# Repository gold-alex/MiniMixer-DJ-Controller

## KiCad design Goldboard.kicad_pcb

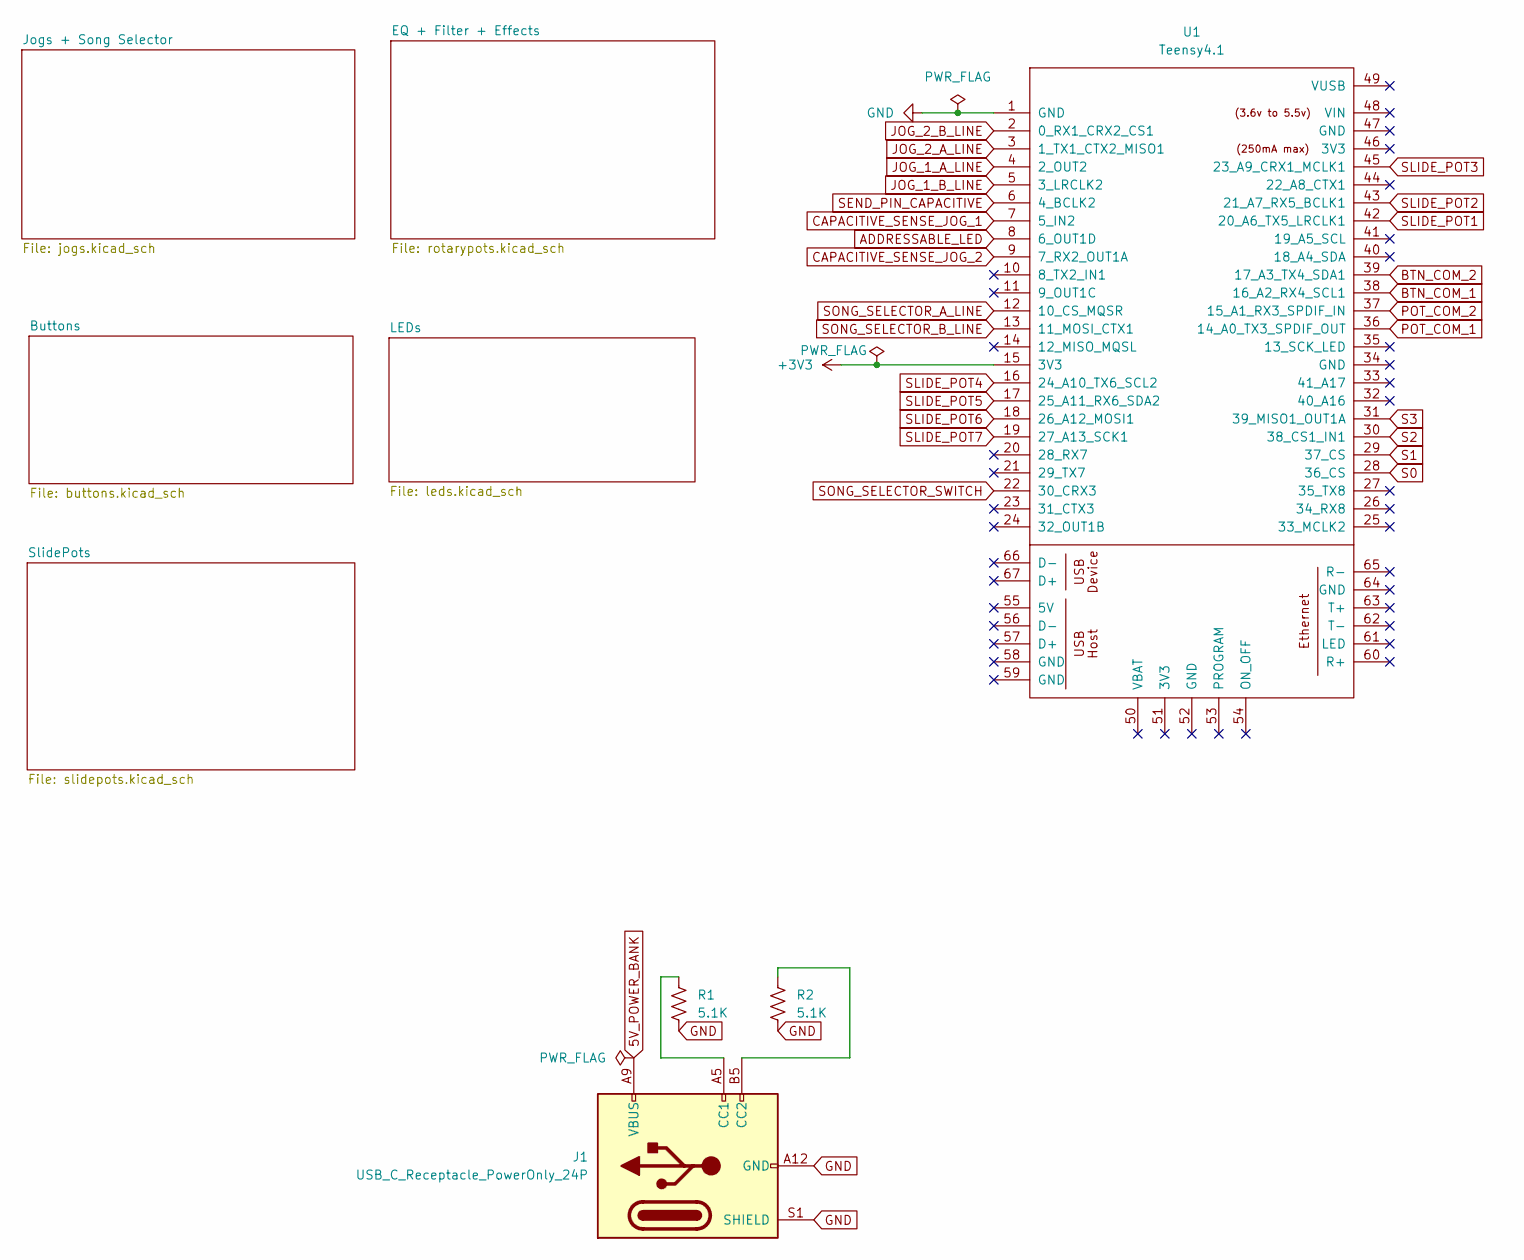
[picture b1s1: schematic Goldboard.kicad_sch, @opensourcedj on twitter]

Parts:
J1: USB_C_Receptacle_PowerOnly_24P; AMPHENOL_12401832E402A
R1, R2: 5.1K; R_0603_1608Metric
U1: Teensy4.1; Teensy41

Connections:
5V_POWER_BANK: J1.A4 (VBUS), J1.A9 (VBUS), J1.B4 (VBUS), J1.B9 (VBUS); also elsewhere on the board
+3V3: U1.15 (3V3); also elsewhere on the board
ADDRESSABLE_LED: U1.8 (6_OUT1D); also elsewhere on the board
BTN_COM_1: U1.38 (16_A2_RX4_SCL1); also elsewhere on the board
BTN_COM_2: U1.39 (17_A3_TX4_SDA1); also elsewhere on the board
CAPACITIVE_SENSE_JOG_1: U1.7 (5_IN2); also elsewhere on the board
CAPACITIVE_SENSE_JOG_2: U1.9 (7_RX2_OUT1A); also elsewhere on the board
GND: J1.A1 (GND), J1.A12 (GND), J1.B1 (GND), J1.B12 (GND), J1.S1 (SHIELD), R1.2, R2.2, U1.1 (GND); also elsewhere on the board
JOG_1_A_LINE: U1.4 (2_OUT2); also elsewhere on the board
JOG_1_B_LINE: U1.5 (3_LRCLK2); also elsewhere on the board
JOG_2_A_LINE: U1.3 (1_TX1_CTX2_MISO1); also elsewhere on the board
JOG_2_B_LINE: U1.2 (0_RX1_CRX2_CS1); also elsewhere on the board
unnamed: J1.A5 (CC1), R1.1
unnamed: J1.B5 (CC2), R2.1
POT_COM_1: U1.36 (14_A0_TX3_SPDIF_OUT); also elsewhere on the board
POT_COM_2: U1.37 (15_A1_RX3_SPDIF_IN); also elsewhere on the board
S0: U1.28 (36_CS); also elsewhere on the board
S1: U1.29 (37_CS); also elsewhere on the board
S2: U1.30 (38_CS1_IN1); also elsewhere on the board
S3: U1.31 (39_MISO1_OUT1A); also elsewhere on the board
SEND_PIN_CAPACITIVE: U1.6 (4_BCLK2); also elsewhere on the board
SLIDE_POT1: U1.42 (20_A6_TX5_LRCLK1); also elsewhere on the board
SLIDE_POT2: U1.43 (21_A7_RX5_BCLK1); also elsewhere on the board
SLIDE_POT3: U1.45 (23_A9_CRX1_MCLK1); also elsewhere on the board
SLIDE_POT4: U1.16 (24_A10_TX6_SCL2); also elsewhere on the board
SLIDE_POT5: U1.17 (25_A11_RX6_SDA2); also elsewhere on the board
SLIDE_POT6: U1.18 (26_A12_MOSI1); also elsewhere on the board
SLIDE_POT7: U1.19 (27_A13_SCK1); also elsewhere on the board
SONG_SELECTOR_A_LINE: U1.12 (10_CS_MQSR); also elsewhere on the board
SONG_SELECTOR_B_LINE: U1.13 (11_MOSI_CTX1); also elsewhere on the board
SONG_SELECTOR_SWITCH: U1.22 (30_CRX3); also elsewhere on the board

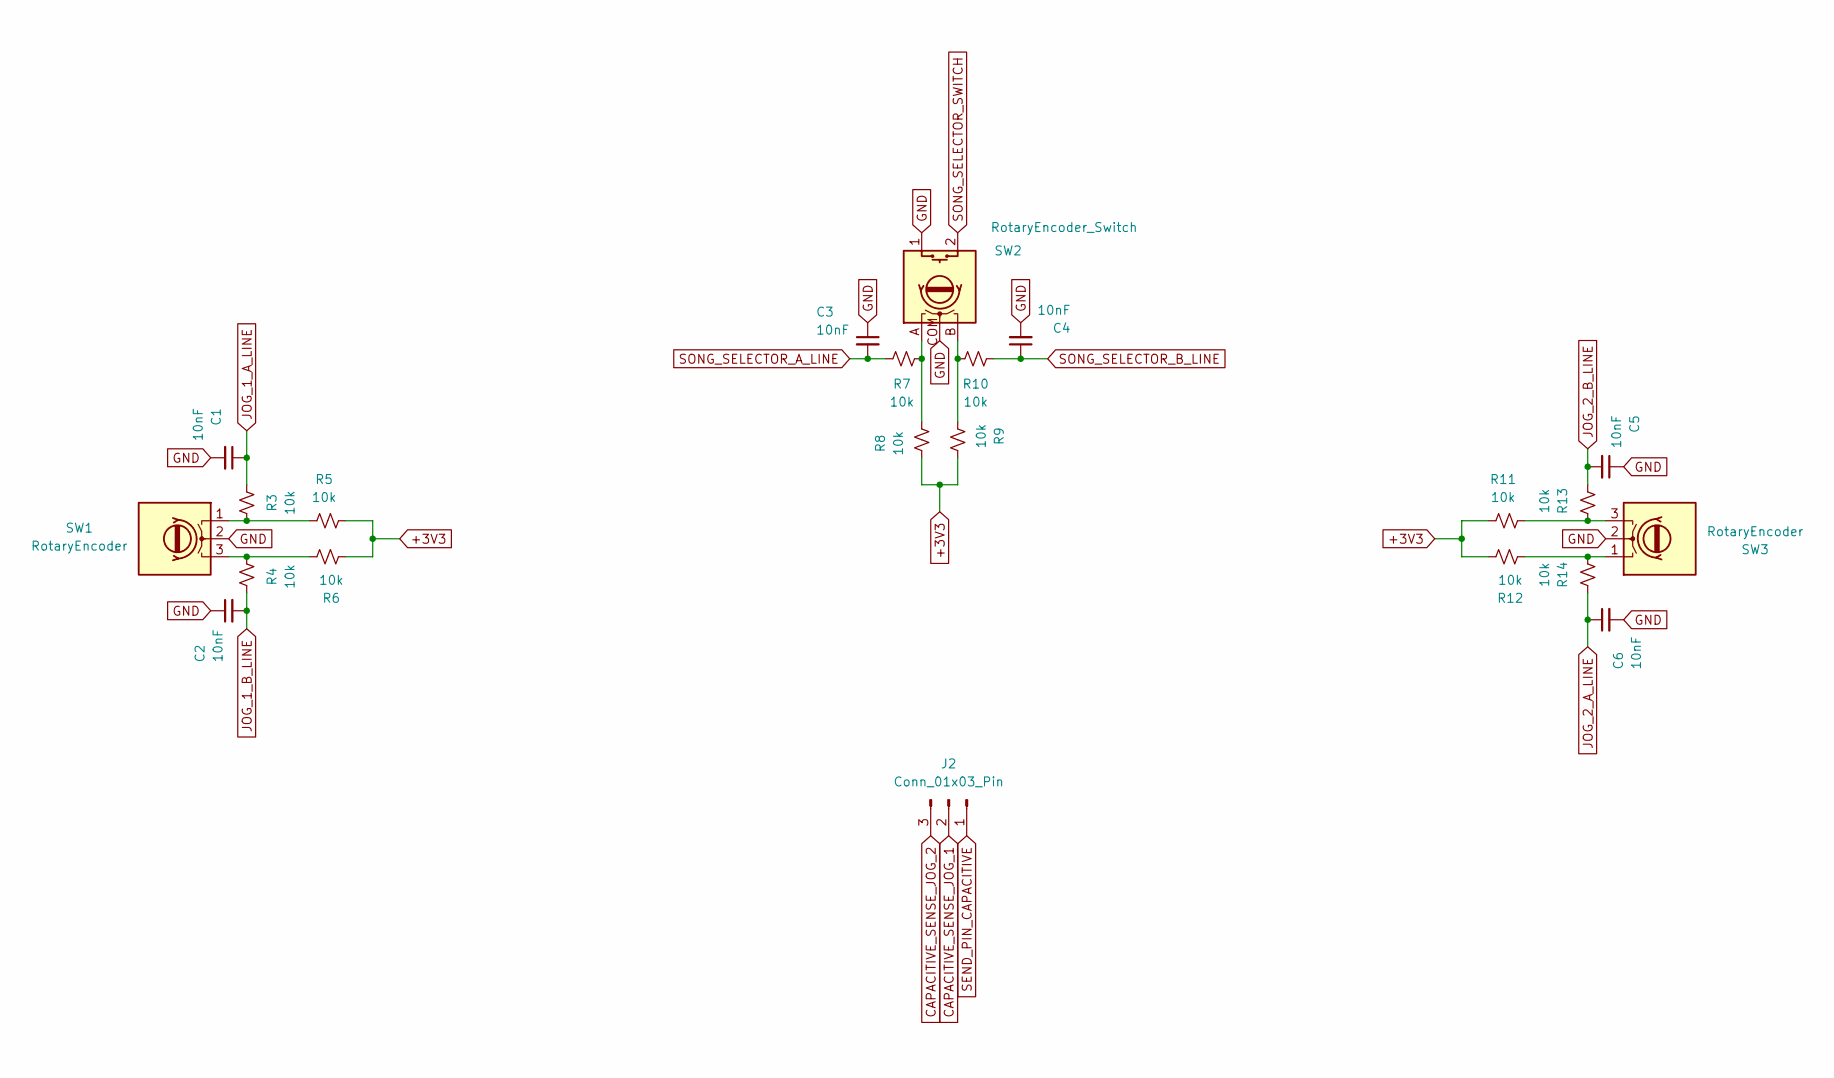
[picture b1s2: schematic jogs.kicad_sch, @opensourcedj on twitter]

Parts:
C1, C2, C3, C4, C5, C6: 10nF; C_0603_1608Metric
J2: Conn_01x03_Pin; PinHeader_1x03_P2.54mm_Horizontal
R3, R4, R5, R6, R7, R8, R9, R10, R11, R12, R13, R14: 10k; R_0603_1608Metric
SW1, SW3: RotaryEncoder; PEC11R-4x15F-Nxxxx_BRN
SW2: RotaryEncoder_Switch; XDCR_PEC11R-4215F-S0024

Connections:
+3V3: R5.1, R6.2, R8.2, R9.1, R11.2, R12.1; also elsewhere on the board
CAPACITIVE_SENSE_JOG_1: J2.2; also elsewhere on the board
CAPACITIVE_SENSE_JOG_2: J2.3; also elsewhere on the board
GND: C1.2, C2.1, C3.1, C4.2, C5.1, C6.2, SW1.2 (C), SW2.1 (S1), SW2.COM (C), SW3.2 (C); also elsewhere on the board
JOG_1_A_LINE: C1.1, R3.1; also elsewhere on the board
JOG_1_B_LINE: C2.2, R4.2; also elsewhere on the board
JOG_2_A_LINE: C6.1, R14.1; also elsewhere on the board
JOG_2_B_LINE: C5.2, R13.2; also elsewhere on the board
unnamed: R7.1, R8.1, SW2.A
unnamed: R9.2, R10.2, SW2.B
unnamed: R3.2, R5.2, SW1.1 (A)
unnamed: R4.1, R6.1, SW1.3 (B)
unnamed: R12.2, R14.2, SW3.1 (A)
unnamed: R11.1, R13.1, SW3.3 (B)
SEND_PIN_CAPACITIVE: J2.1; also elsewhere on the board
SONG_SELECTOR_A_LINE: C3.2, R7.2; also elsewhere on the board
SONG_SELECTOR_B_LINE: C4.1, R10.1; also elsewhere on the board
SONG_SELECTOR_SWITCH: SW2.2 (S2); also elsewhere on the board

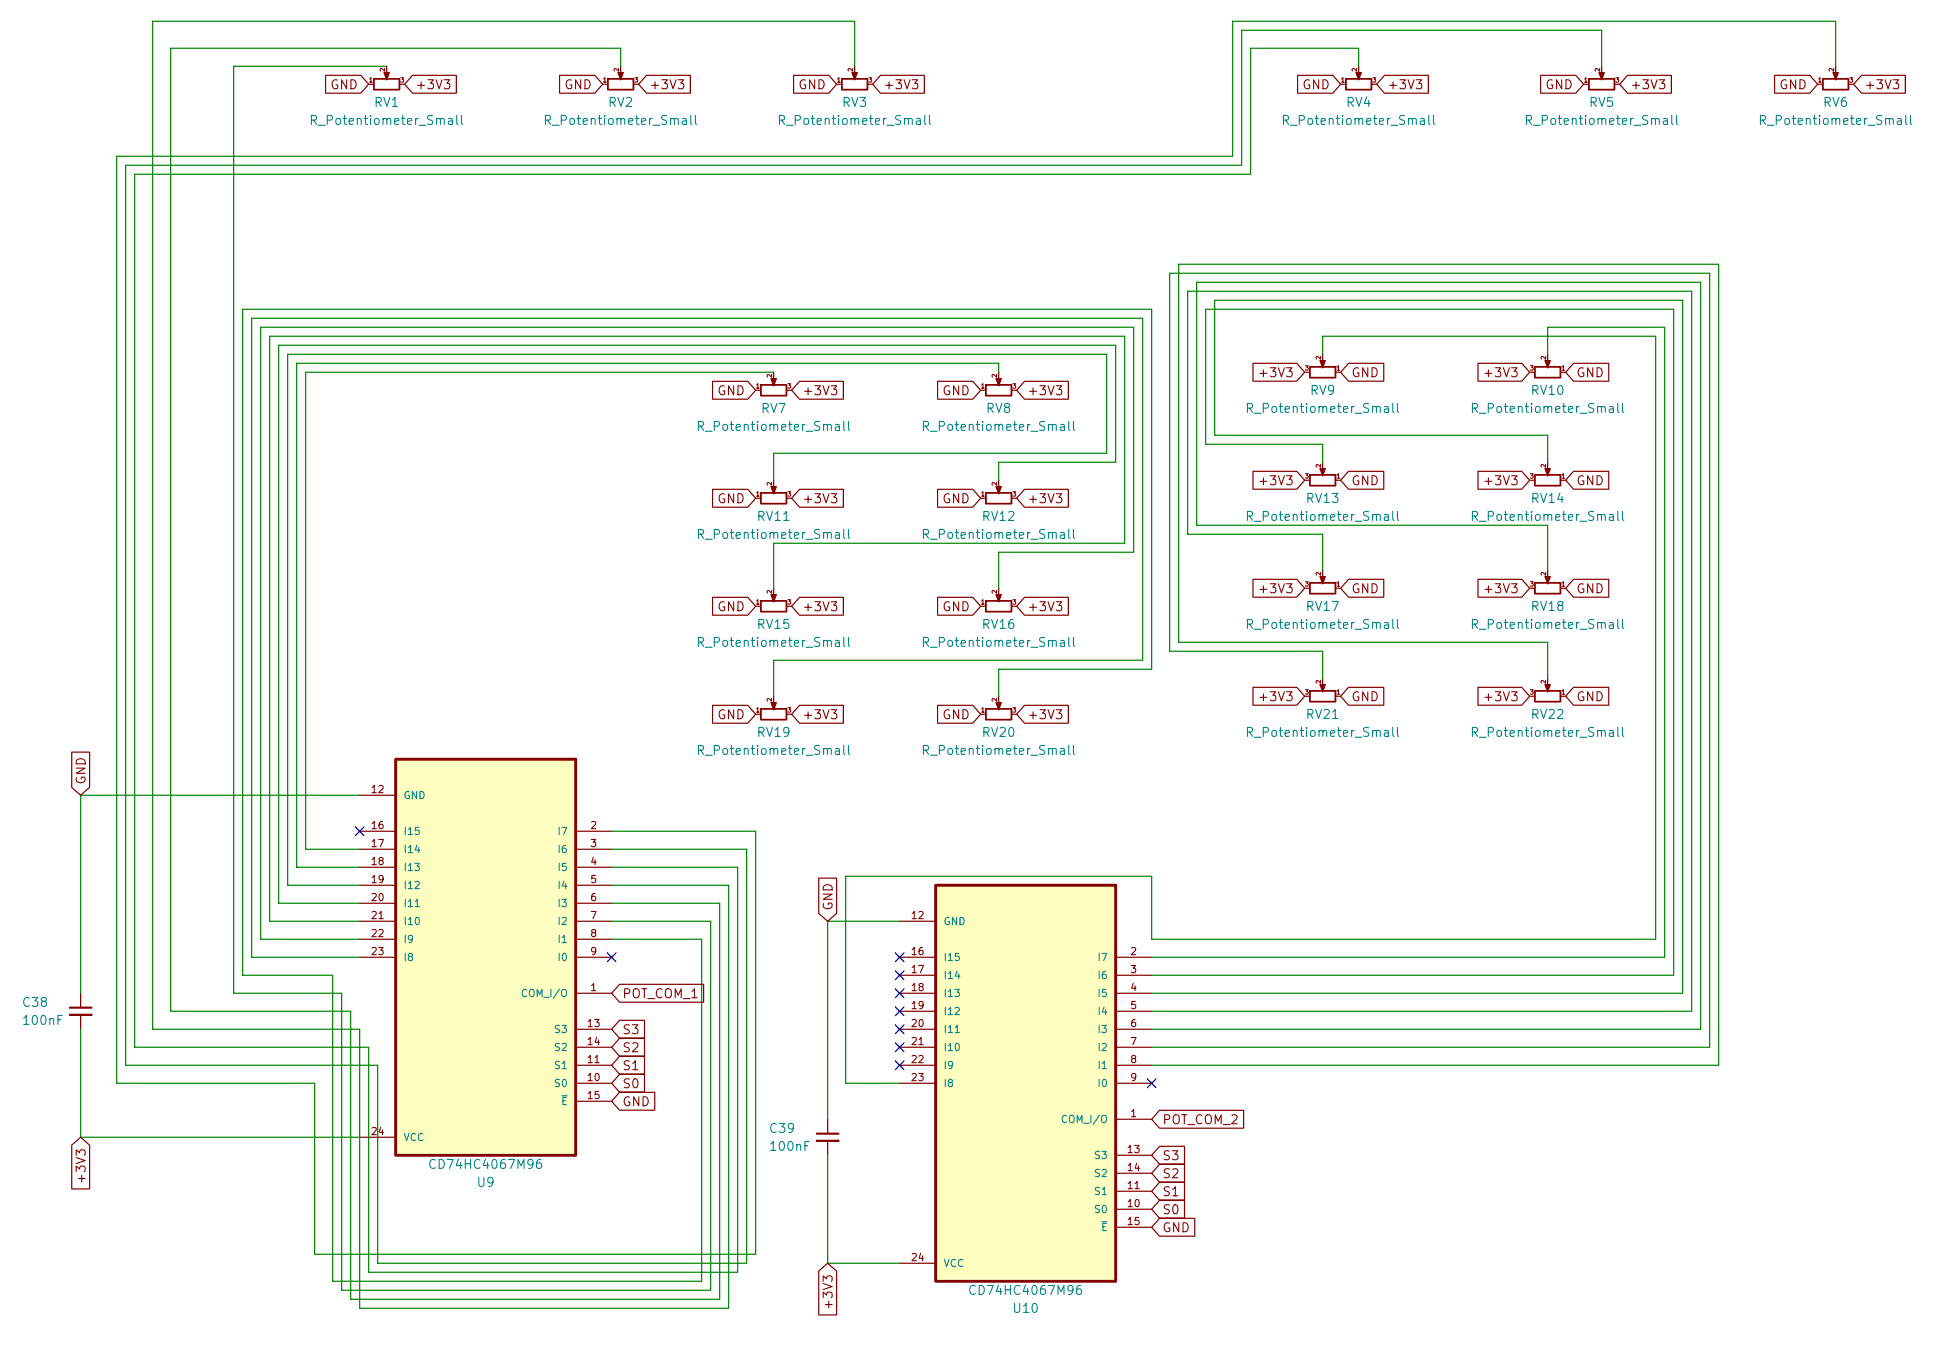
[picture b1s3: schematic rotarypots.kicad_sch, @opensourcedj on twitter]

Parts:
C38, C39: 100nF; C_0603_1608Metric
RV1, RV2, RV3, RV4, RV5, RV6, RV7, RV8, RV9, RV10, RV11, RV12, RV13, RV14, RV15, RV16, RV17, RV18, RV19, RV20, RV21, RV22: R_Potentiometer_Small; RK09D1130C3W_using_RK09D1130009_footprint_ALPS
U9, U10: CD74HC4067M96; SOIC127P1030X265-24N

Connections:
+3V3: C38.2, C39.2, RV1.3, RV2.3, RV3.3, RV4.3, RV5.3, RV6.3, RV7.3, RV8.3, RV9.3, RV10.3, RV11.3, RV12.3, RV13.3, RV14.3, RV15.3, RV16.3, RV17.3, RV18.3, RV19.3, RV20.3, RV21.3, RV22.3, U9.24 (VCC), U10.24 (VCC); also elsewhere on the board
GND: C38.1, C39.1, RV1.1, RV2.1, RV3.1, RV4.1, RV5.1, RV6.1, RV7.1, RV8.1, RV9.1, RV10.1, RV11.1, RV12.1, RV13.1, RV14.1, RV15.1, RV16.1, RV17.1, RV18.1, RV19.1, RV20.1, RV21.1, RV22.1, U9.12 (GND), U9.15 (~E), U10.12 (GND), U10.15 (~E); also elsewhere on the board
unnamed: RV20.2, U9.8 (I1)
unnamed: RV1.2, U9.7 (I2)
unnamed: RV2.2, U9.6 (I3)
unnamed: RV3.2, U9.5 (I4)
unnamed: RV4.2, U9.4 (I5)
unnamed: RV5.2, U9.3 (I6)
unnamed: RV6.2, U9.2 (I7)
unnamed: RV19.2, U9.23 (I8)
unnamed: RV16.2, U9.22 (I9)
unnamed: RV15.2, U9.21 (I10)
unnamed: RV12.2, U9.20 (I11)
unnamed: RV11.2, U9.19 (I12)
unnamed: RV8.2, U9.18 (I13)
unnamed: RV7.2, U9.17 (I14)
unnamed: RV22.2, U10.8 (I1)
unnamed: RV21.2, U10.7 (I2)
unnamed: RV18.2, U10.6 (I3)
unnamed: RV17.2, U10.5 (I4)
unnamed: RV14.2, U10.4 (I5)
unnamed: RV13.2, U10.3 (I6)
unnamed: RV10.2, U10.2 (I7)
unnamed: RV9.2, U10.23 (I8)
POT_COM_1: U9.1 (COM_I/O); also elsewhere on the board
POT_COM_2: U10.1 (COM_I/O); also elsewhere on the board
S0: U9.10 (S0), U10.10 (S0); also elsewhere on the board
S1: U9.11 (S1), U10.11 (S1); also elsewhere on the board
S2: U9.14 (S2), U10.14 (S2); also elsewhere on the board
S3: U9.13 (S3), U10.13 (S3); also elsewhere on the board

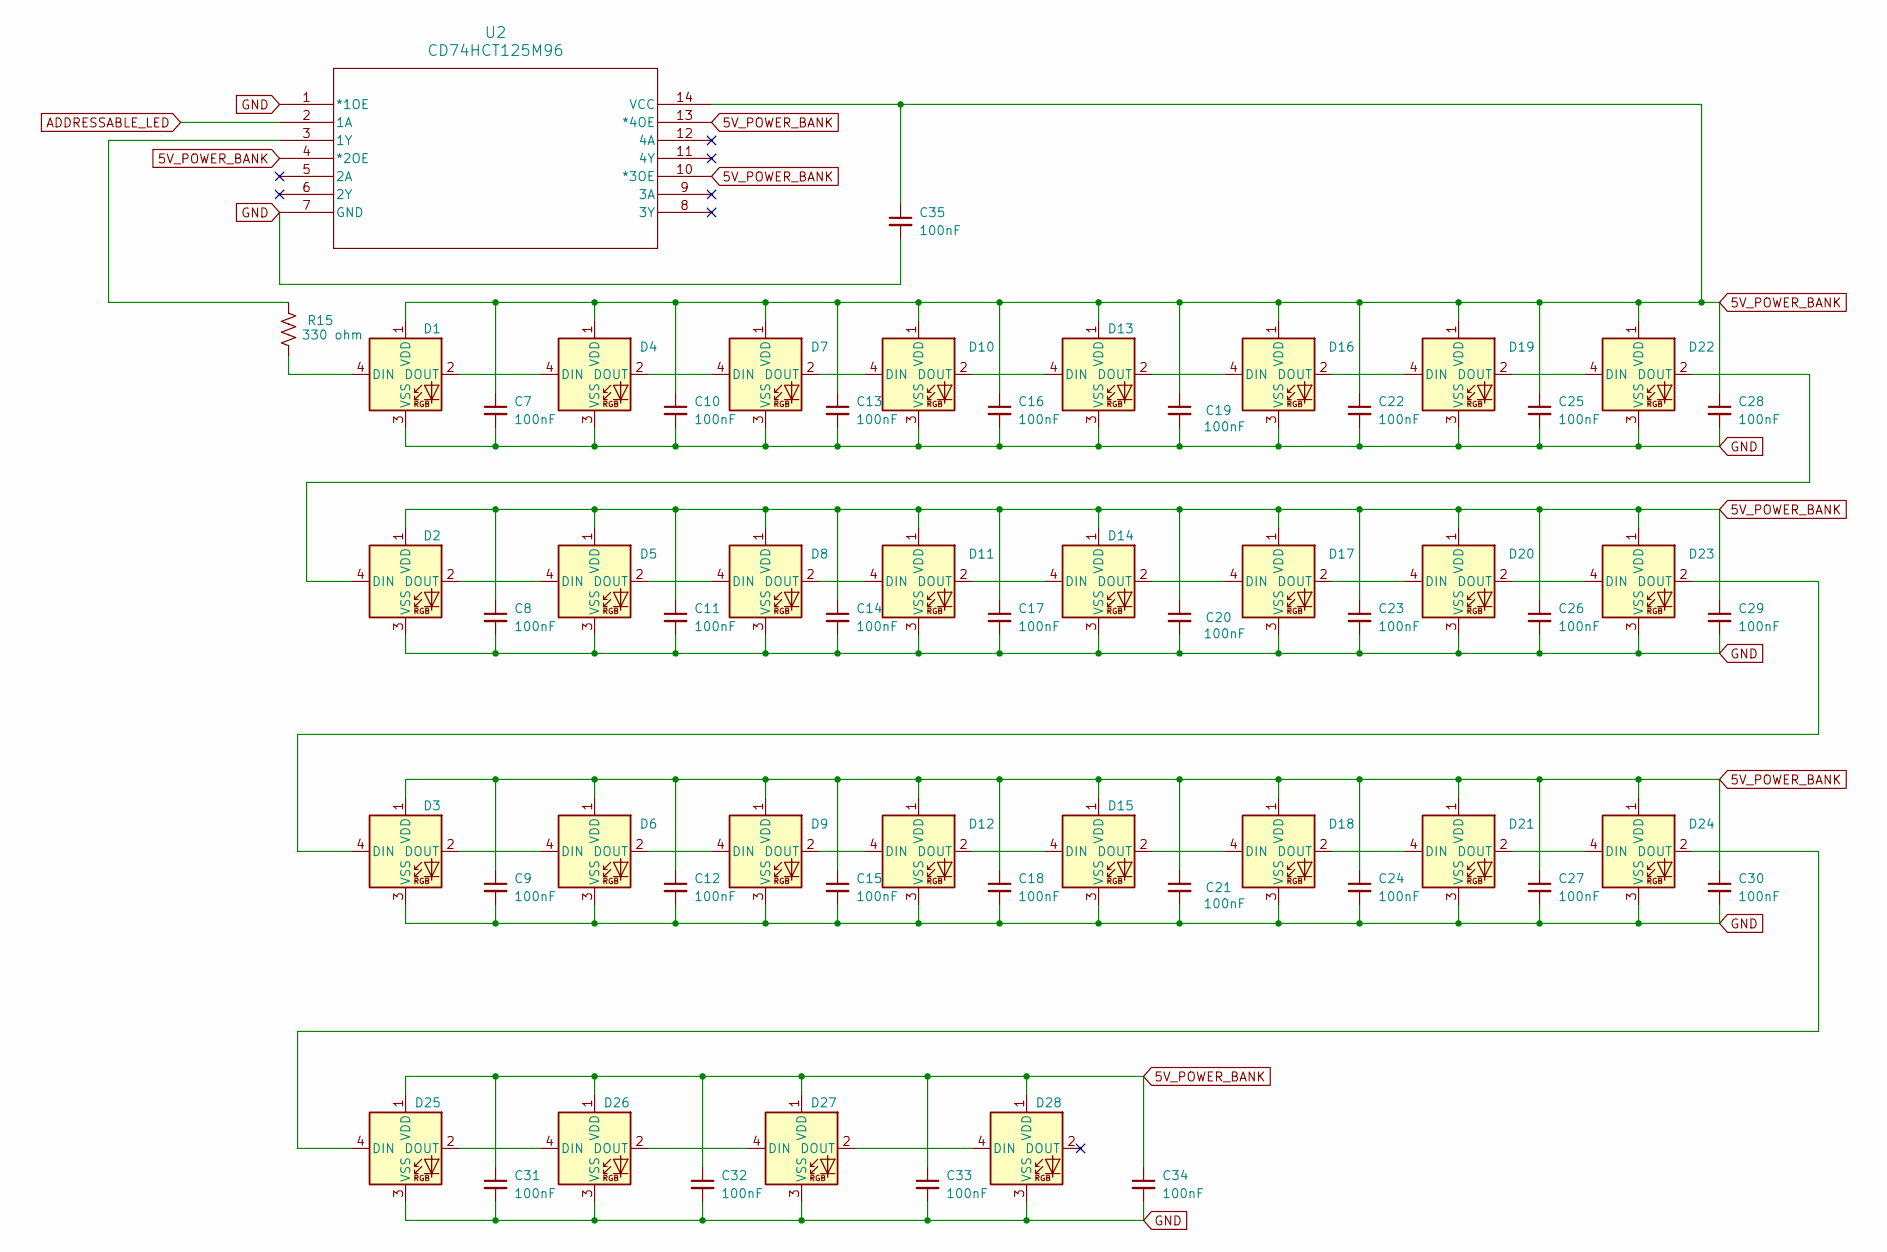
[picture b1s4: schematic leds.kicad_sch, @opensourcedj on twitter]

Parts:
C7, C8, C9, C10, C11, C12, C13, C14, C15, C16, C17, C18, C19, C20, C21, C22, C23, C24, C25, C26, C27, C28, C29, C30, C31, C32, C33, C34, C35: 100nF; C_0603_1608Metric
D1, D2, D3, D4, D5, D6, D7, D8, D9, D10, D11, D12, D13, D14, D15, D16, D17, D18, D19, D20, D21, D22, D23, D24, D25, D26, D27, D28: WS2812B_passive_vss; LED_WS2812B_PLCC4_5.0x5.0mm_P3.2mm
R15: 330 ohm; R_0603_1608Metric
U2: CD74HCT125M96; D14

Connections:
5V_POWER_BANK: C7.1, C8.1, C9.1, C10.1, C11.1, C12.1, C13.1, C14.1, C15.1, C16.1, C17.1, C18.1, C19.1, C20.1, C21.1, C22.1, C23.1, C24.1, C25.1, C26.1, C27.1, C28.1, C29.1, C30.1, C31.1, C32.1, C33.1, C34.1, C35.1, D1.1 (VDD), D2.1 (VDD), D3.1 (VDD), D4.1 (VDD), D5.1 (VDD), D6.1 (VDD), D7.1 (VDD), D8.1 (VDD), D9.1 (VDD), D10.1 (VDD), D11.1 (VDD), D12.1 (VDD), D13.1 (VDD), D14.1 (VDD), D15.1 (VDD), D16.1 (VDD), D17.1 (VDD), D18.1 (VDD), D19.1 (VDD), D20.1 (VDD), D21.1 (VDD), D22.1 (VDD), D23.1 (VDD), D24.1 (VDD), D25.1 (VDD), D26.1 (VDD), D27.1 (VDD), D28.1 (VDD), U2.4 (*2OE), U2.10 (*3OE), U2.13 (*4OE), U2.14 (VCC); also elsewhere on the board
ADDRESSABLE_LED: U2.2 (1A); also elsewhere on the board
GND: C7.2, C8.2, C9.2, C10.2, C11.2, C12.2, C13.2, C14.2, C15.2, C16.2, C17.2, C18.2, C19.2, C20.2, C21.2, C22.2, C23.2, C24.2, C25.2, C26.2, C27.2, C28.2, C29.2, C30.2, C31.2, C32.2, C33.2, C34.2, C35.2, D1.3 (VSS), D2.3 (VSS), D3.3 (VSS), D4.3 (VSS), D5.3 (VSS), D6.3 (VSS), D7.3 (VSS), D8.3 (VSS), D9.3 (VSS), D10.3 (VSS), D11.3 (VSS), D12.3 (VSS), D13.3 (VSS), D14.3 (VSS), D15.3 (VSS), D16.3 (VSS), D17.3 (VSS), D18.3 (VSS), D19.3 (VSS), D20.3 (VSS), D21.3 (VSS), D22.3 (VSS), D23.3 (VSS), D24.3 (VSS), D25.3 (VSS), D26.3 (VSS), D27.3 (VSS), D28.3 (VSS), U2.1 (*1OE), U2.7 (GND); also elsewhere on the board
unnamed: D1.4 (DIN), R15.2
unnamed: D1.2 (DOUT), D4.4 (DIN)
unnamed: D2.4 (DIN), D22.2 (DOUT)
unnamed: D2.2 (DOUT), D5.4 (DIN)
unnamed: D3.2 (DOUT), D6.4 (DIN)
unnamed: D4.2 (DOUT), D7.4 (DIN)
unnamed: D5.2 (DOUT), D8.4 (DIN)
unnamed: D6.2 (DOUT), D9.4 (DIN)
unnamed: D7.2 (DOUT), D10.4 (DIN)
unnamed: D10.2 (DOUT), D13.4 (DIN)
unnamed: D8.2 (DOUT), D11.4 (DIN)
unnamed: D11.2 (DOUT), D14.4 (DIN)
unnamed: D9.2 (DOUT), D12.4 (DIN)
unnamed: D12.2 (DOUT), D15.4 (DIN)
unnamed: D13.2 (DOUT), D16.4 (DIN)
unnamed: D14.2 (DOUT), D17.4 (DIN)
unnamed: D15.2 (DOUT), D18.4 (DIN)
unnamed: D16.2 (DOUT), D19.4 (DIN)
unnamed: D17.2 (DOUT), D20.4 (DIN)
unnamed: D18.2 (DOUT), D21.4 (DIN)
unnamed: D19.2 (DOUT), D22.4 (DIN)
unnamed: D20.2 (DOUT), D23.4 (DIN)
unnamed: D21.2 (DOUT), D24.4 (DIN)
unnamed: D3.4 (DIN), D23.2 (DOUT)
unnamed: D24.2 (DOUT), D25.4 (DIN)
unnamed: D25.2 (DOUT), D26.4 (DIN)
unnamed: D26.2 (DOUT), D27.4 (DIN)
unnamed: D27.2 (DOUT), D28.4 (DIN)
unnamed: R15.1, U2.3 (1Y)

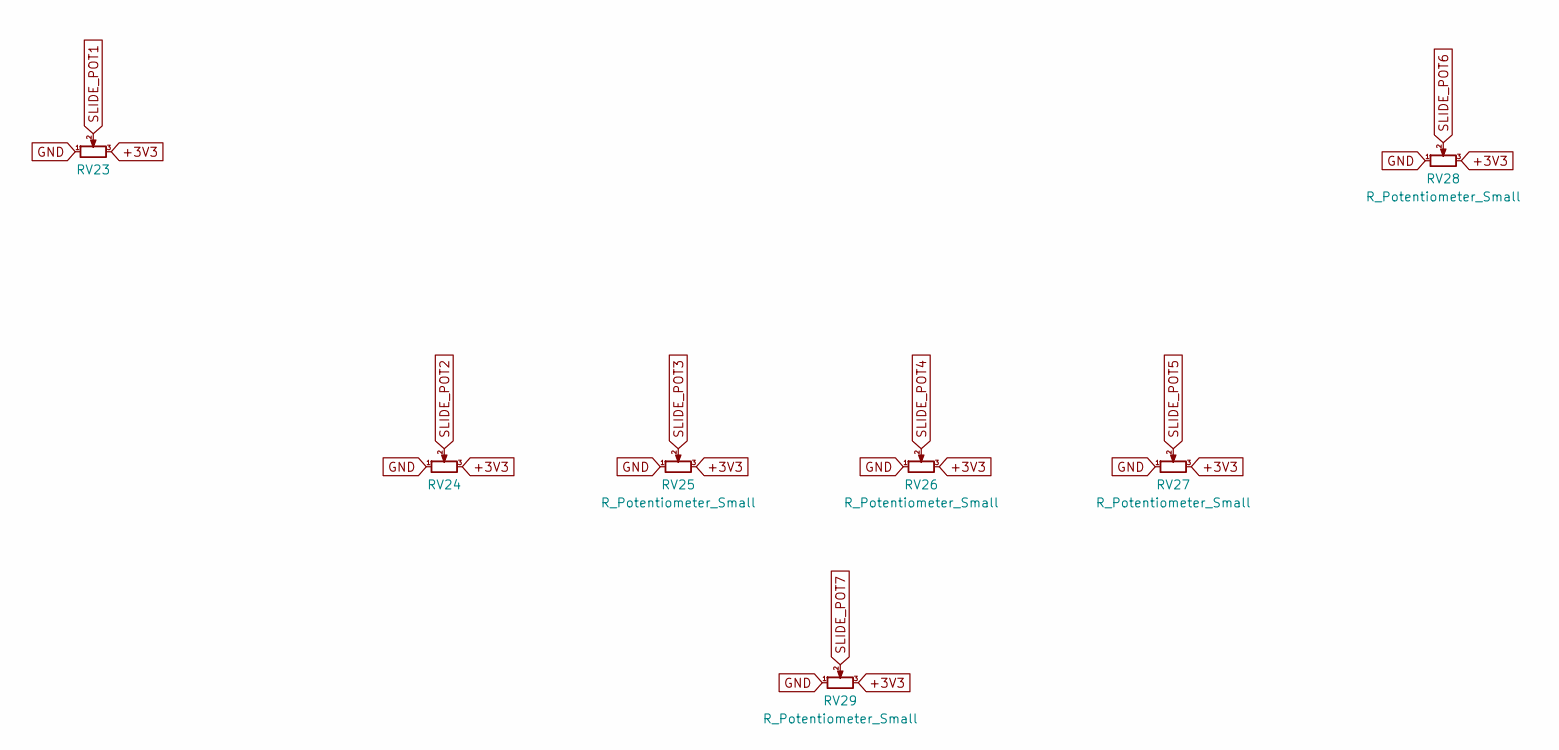
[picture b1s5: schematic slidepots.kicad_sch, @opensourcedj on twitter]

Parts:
RV23, RV24, RV25, RV26, RV27, RV28: R_Potentiometer_Small; Potentiometer_Bourns_PTA1543_Single_Slide
RV29: R_Potentiometer_Small; Potentiometer_Bourns_PTA6043_Single_Slide

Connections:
+3V3: RV23.3, RV24.3, RV25.3, RV26.3, RV27.3, RV28.3, RV29.3; also elsewhere on the board
GND: RV23.1, RV24.1, RV25.1, RV26.1, RV27.1, RV28.1, RV29.1; also elsewhere on the board
SLIDE_POT1: RV23.2; also elsewhere on the board
SLIDE_POT2: RV24.2; also elsewhere on the board
SLIDE_POT3: RV25.2; also elsewhere on the board
SLIDE_POT4: RV26.2; also elsewhere on the board
SLIDE_POT5: RV27.2; also elsewhere on the board
SLIDE_POT6: RV28.2; also elsewhere on the board
SLIDE_POT7: RV29.2; also elsewhere on the board

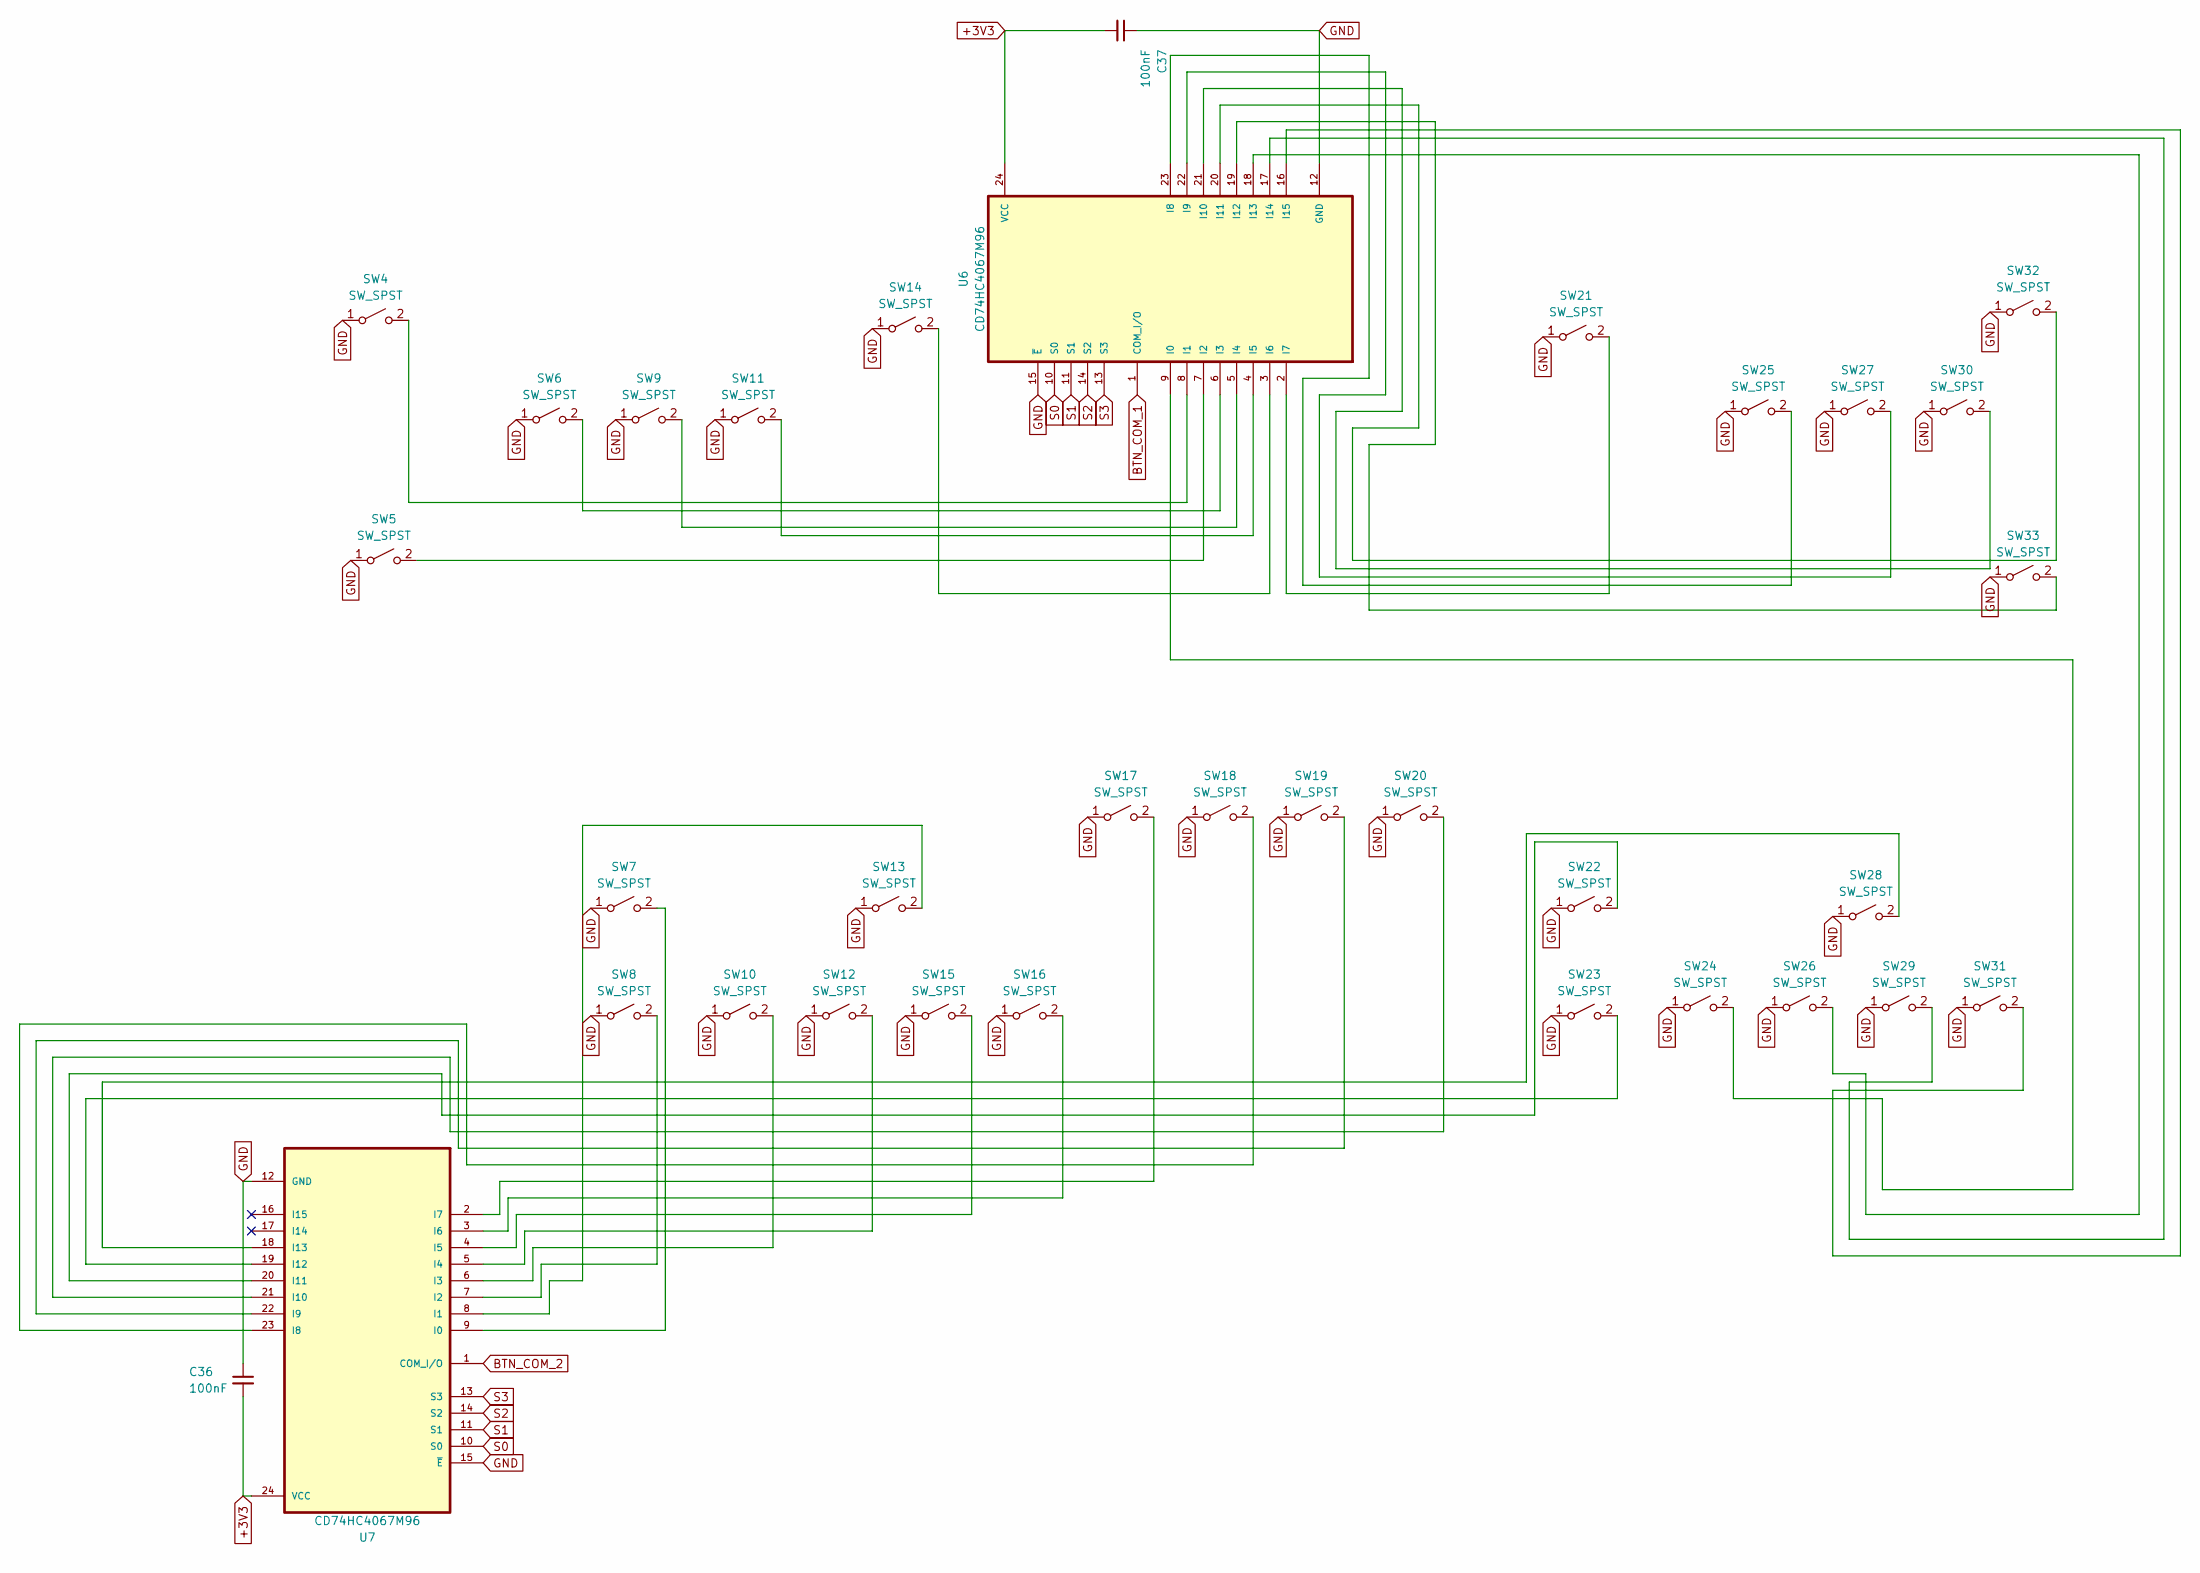
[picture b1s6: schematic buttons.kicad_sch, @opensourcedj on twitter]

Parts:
C36, C37: 100nF; C_0603_1608Metric
SW4, SW5, SW6, SW7, SW8, SW9, SW11, SW13, SW14, SW17, SW18, SW19, SW20, SW21, SW22, SW23, SW25, SW27, SW28, SW30, SW32, SW33: SW_SPST; SW_TS-1088-AR02016
SW10, SW12, SW15, SW16, SW24, SW26, SW29, SW31: SW_SPST; BUTTONPAD-1x1
U6, U7: CD74HC4067M96; SOIC127P1030X265-24N

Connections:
+3V3: C36.2, C37.2, U6.24 (VCC), U7.24 (VCC); also elsewhere on the board
BTN_COM_1: U6.1 (COM_I/O); also elsewhere on the board
BTN_COM_2: U7.1 (COM_I/O); also elsewhere on the board
GND: C36.1, C37.1, SW4.1 (A), SW5.1 (A), SW6.1 (A), SW7.1 (A), SW8.1 (A), SW9.1 (A), SW10.1 (A), SW11.1 (A), SW12.1 (A), SW13.1 (A), SW14.1 (A), SW15.1 (A), SW16.1 (A), SW17.1 (A), SW18.1 (A), SW19.1 (A), SW20.1 (A), SW21.1 (A), SW22.1 (A), SW23.1 (A), SW24.1 (A), SW25.1 (A), SW26.1 (A), SW27.1 (A), SW28.1 (A), SW29.1 (A), SW30.1 (A), SW31.1 (A), SW32.1 (A), SW33.1 (A), U6.12 (GND), U6.15 (~E), U7.12 (GND), U7.15 (~E); also elsewhere on the board
unnamed: SW4.2 (B), U6.8 (I1)
unnamed: SW5.2 (B), U6.7 (I2)
unnamed: SW6.2 (B), U6.6 (I3)
unnamed: SW7.2 (B), U7.9 (I0)
unnamed: SW8.2 (B), U7.7 (I2)
unnamed: SW9.2 (B), U6.5 (I4)
unnamed: SW10.2 (B), U7.6 (I3)
unnamed: SW11.2 (B), U6.4 (I5)
unnamed: SW12.2 (B), U7.5 (I4)
unnamed: SW13.2 (B), U7.8 (I1)
unnamed: SW14.2 (B), U6.3 (I6)
unnamed: SW15.2 (B), U7.4 (I5)
unnamed: SW16.2 (B), U7.3 (I6)
unnamed: SW17.2 (B), U7.2 (I7)
unnamed: SW18.2 (B), U7.23 (I8)
unnamed: SW19.2 (B), U7.22 (I9)
unnamed: SW20.2 (B), U7.21 (I10)
unnamed: SW21.2 (B), U6.2 (I7)
unnamed: SW22.2 (B), U7.20 (I11)
unnamed: SW23.2 (B), U7.19 (I12)
unnamed: SW24.2 (B), U6.9 (I0)
unnamed: SW25.2 (B), U6.23 (I8)
unnamed: SW26.2 (B), U6.18 (I13)
unnamed: SW27.2 (B), U6.22 (I9)
unnamed: SW28.2 (B), U7.18 (I13)
unnamed: SW29.2 (B), U6.17 (I14)
unnamed: SW30.2 (B), U6.21 (I10)
unnamed: SW31.2 (B), U6.16 (I15)
unnamed: SW32.2 (B), U6.20 (I11)
unnamed: SW33.2 (B), U6.19 (I12)
S0: U6.10 (S0), U7.10 (S0); also elsewhere on the board
S1: U6.11 (S1), U7.11 (S1); also elsewhere on the board
S2: U6.14 (S2), U7.14 (S2); also elsewhere on the board
S3: U6.13 (S3), U7.13 (S3); also elsewhere on the board

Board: 2 copper layers, 152 parts (0 on the bottom side), 118 nets, no tracks yet.

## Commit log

2025-03-14 organizing
2025-03-14 organizing further
